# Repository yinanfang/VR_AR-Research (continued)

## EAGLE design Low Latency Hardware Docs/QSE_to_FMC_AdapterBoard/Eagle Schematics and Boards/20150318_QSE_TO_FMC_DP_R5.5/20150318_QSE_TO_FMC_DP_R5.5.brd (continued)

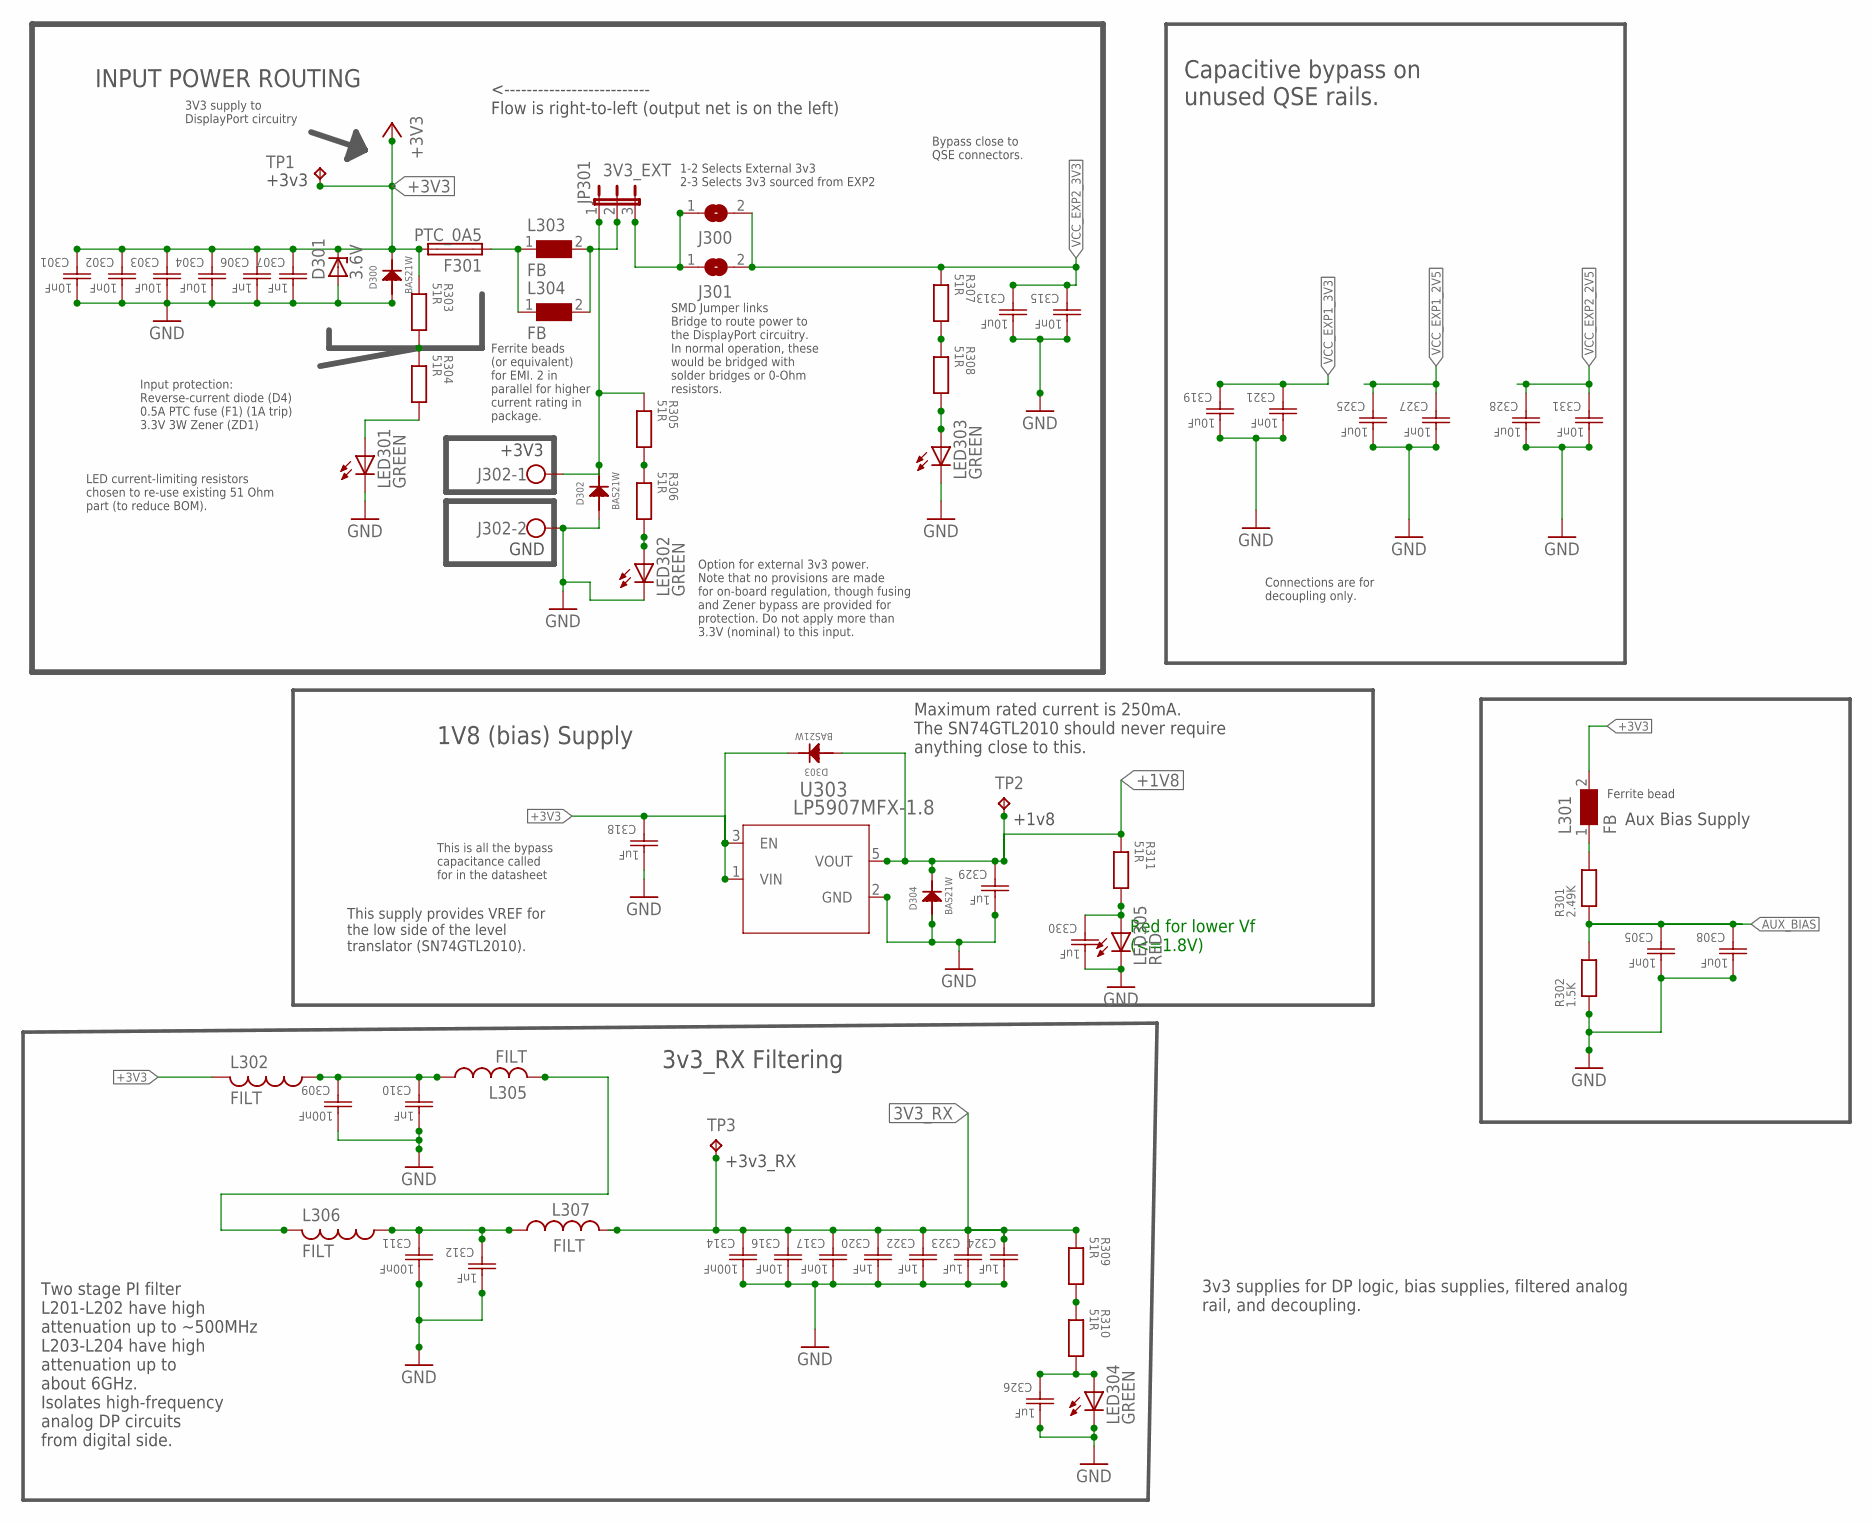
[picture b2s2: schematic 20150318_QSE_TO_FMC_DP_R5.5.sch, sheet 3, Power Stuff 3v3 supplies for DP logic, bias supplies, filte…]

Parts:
C301, C302: 10nF; CAPC1005X60N
C303, C304, C308, C313, C319, C325, C328: 10uF; CAPC1608X85N
C305, C316, C317: 10nF; CAPC1005X60N; PART# GRM1885C1H103JA01
C306, C307, C310, C312, C320, C322: 1nF; CAPC1005X60N; PART# GRM1885C1E102JA01
C309, C311, C314: 100nF; CAPC1005X60N; PART# GRM188B31H104MA92
C315, C321, C327, C331: 10nF; CAPC1608X85N
C318, C329: 1uF; CAPC1005X60N
C323, C324, C326, C330: 1uF; CAPC1005X60N; PART# GRM188B31A225KE33
D300, D302, D303, D304: BAS21W; SOT65P210X100-3N
D301: 3.6V; SMB; PART# 1SMB5914BT3G
F301: PTC_0A5; SMD-0805
J300, J301: SJW
J302: W237-102
JP301: 3V3_EXT; JP2
L301: FB; 0402
L302, L305: FILT; R0603; PART# BLM18HE152SN1
L303, L304: FB; 0805
L306, L307: FILT; R0603; PART# BLM18HE601SN1
LED301, LED302, LED303, LED304: GREEN; CHIP-LED0805; PART# LG R971-KN-1; DIGIKEY_SKU 475-1410-1-ND
LED305: RED; SML0603; PART# 5975112407F; DIGIKEY_SKU 350-2436-6-ND
R301: 2.49K; RESC1005X40N
R302: 1.5K; RESC1005X40N
R303, R304, R305, R306, R307, R308, R309, R310, R311: 51R; RESC1005X40N
TP1: +3v3; TP10R
TP2: +1v8; TP10R
TP3: +3v3_RX; TP10R
U303: LP5907MFX-1.8; DBV5

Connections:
1V8_LED: C330.2 (1), LED305.A, R311.1
3V3_EXP_JP: D302.3 (C), J302.1, JP301.1, R305.2
3V3_INT_JP: J300.1, J301.1, JP301.3
3V3_INT_LED: LED303.A, R308.1
3V3_IN_FILTER_TO_FUSE: F301.1, L303.1, L304.1
3V3_RX: C314.2 (1), C316.2 (1), C317.2 (1), C320.2 (1), C322.2 (1), C323.2 (1), C324.2 (1), L307.2, R309.2, TP3.TP; also elsewhere on the board
3V3_RX_FILT_S0: C309.2 (1), C310.2 (1), L302.1, L305.1
3V3_RX_FILT_S1: L305.2, L306.2
3V3_RX_FILT_S2: C311.2 (1), C312.2 (1), L306.1, L307.1
3V3_RX_LED: C326.2 (1), LED304.A, R310.1
3V3_TO_AUX_BIAS_POST_FILTER: L301.1, R301.1
+1V8: C329.2 (1), D303.1 (A), D304.3 (C), R311.2, TP2.TP, U303.5 (VOUT); also elsewhere on the board
+3V3: C301.2 (1), C302.2 (1), C303.2 (1), C304.2 (1), C306.2 (1), C307.2 (1), C318.2 (1), D300.3 (C), D301.C, D303.3 (C), F301.2, L301.2, L302.2, R303.2, TP1.TP, U303.1 (VIN), U303.3 (EN); also elsewhere on the board
AUX_BIAS: C305.2 (1), C308.2 (1), R301.2, R302.1; also elsewhere on the board
EXT_3V3_LED: LED302.A, R306.1
GND: C301.1 (2), C302.1 (2), C303.1 (2), C304.1 (2), C305.1 (2), C306.1 (2), C307.1 (2), C308.1 (2), C309.1 (2), C310.1 (2), C311.1 (2), C312.1 (2), C313.1 (2), C314.1 (2), C315.1 (2), C316.1 (2), C317.1 (2), C318.1 (2), C319.1 (2), C320.1 (2), C321.1 (2), C322.1 (2), C323.1 (2), C324.1 (2), C325.1 (2), C326.1 (2), C327.1 (2), C328.1 (2), C329.1 (2), C330.1 (2), C331.1 (2), D300.1 (A), D301.A, D302.1 (A), D304.1 (A), J302.2, LED301.C, LED302.C, LED303.C, LED304.C, LED305.C, R302.2, U303.2 (GND); also elsewhere on the board
MAIN_POWER_LED: LED301.A, R304.1
R303_R304: R303.1, R304.2
R306_R305: R305.1, R306.2
R308_R307: R307.1, R308.2
R309_R310: R309.1, R310.2
SELECTED_3V3: JP301.2, L303.2, L304.2
VCC_EXP1_2V5: C325.2 (1), C327.2 (1); also elsewhere on the board
VCC_EXP1_3V3: C319.2 (1), C321.2 (1); also elsewhere on the board
VCC_EXP2_2V5: C328.2 (1), C331.2 (1); also elsewhere on the board
VCC_EXP2_3V3: C313.2 (1), C315.2 (1), J300.2, J301.2, R307.2; also elsewhere on the board

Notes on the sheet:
This supply provides VREF for the low side of the level translator (SN74GTL2010).
Aux Bias Supply
1-2 Selects External 3v3 2-3 Selects 3v3 sourced from EXP2
INPUT POWER ROUTING
SMD Jumper links Bridge to route power to the DisplayPort circuitry. In normal operation, these would be bridged with solder bridges or 0-Ohm resistors.
+3V3
GND
Option for external 3v3 power. Note that no provisions are made for on-board regulation, though fusing and Zener bypass are provided for protection. Do not apply more than 3.3V (nominal) to this input.
Input protection: Reverse-current diode (D4) 0.5A PTC fuse (F1) (1A trip) 3.3V 3W Zener (ZD1)
3V3 supply to DisplayPort circuitry
Bypass close to QSE connectors.
Two stage PI filter L201-L202 have high attenuation up to ~500MHz L203-L204 have high attenuation up to about 6GHz. Isolates high-frequency analog DP circuits from digital side.
Maximum rated current is 250mA. The SN74GTL2010 should never require anything close to this.
This is all the bypass capacitance called for in the datasheet
3v3_RX Filtering
1V8 (bias) Supply
Red for lower Vf (<=1.8V)
Connections are for decoupling only.
Ferrite beads (or equivalent) for EMI. 2 in parallel for higher current rating in package.
LED current-limiting resistors chosen to re-use existing 51 Ohm part (to reduce BOM).
<-------------------------- Flow is right-to-left (output net is on the left)
Ferrite bead
Capacitive bypass on unused QSE rails.
3v3 supplies for DP logic, bias supplies, filtered analog rail, and decoupling.

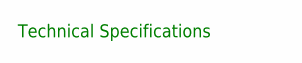
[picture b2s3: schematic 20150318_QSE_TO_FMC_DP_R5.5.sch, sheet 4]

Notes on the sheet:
Technical Specifications

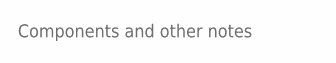
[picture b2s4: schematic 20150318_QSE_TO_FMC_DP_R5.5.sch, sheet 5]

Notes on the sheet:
Components and other notes

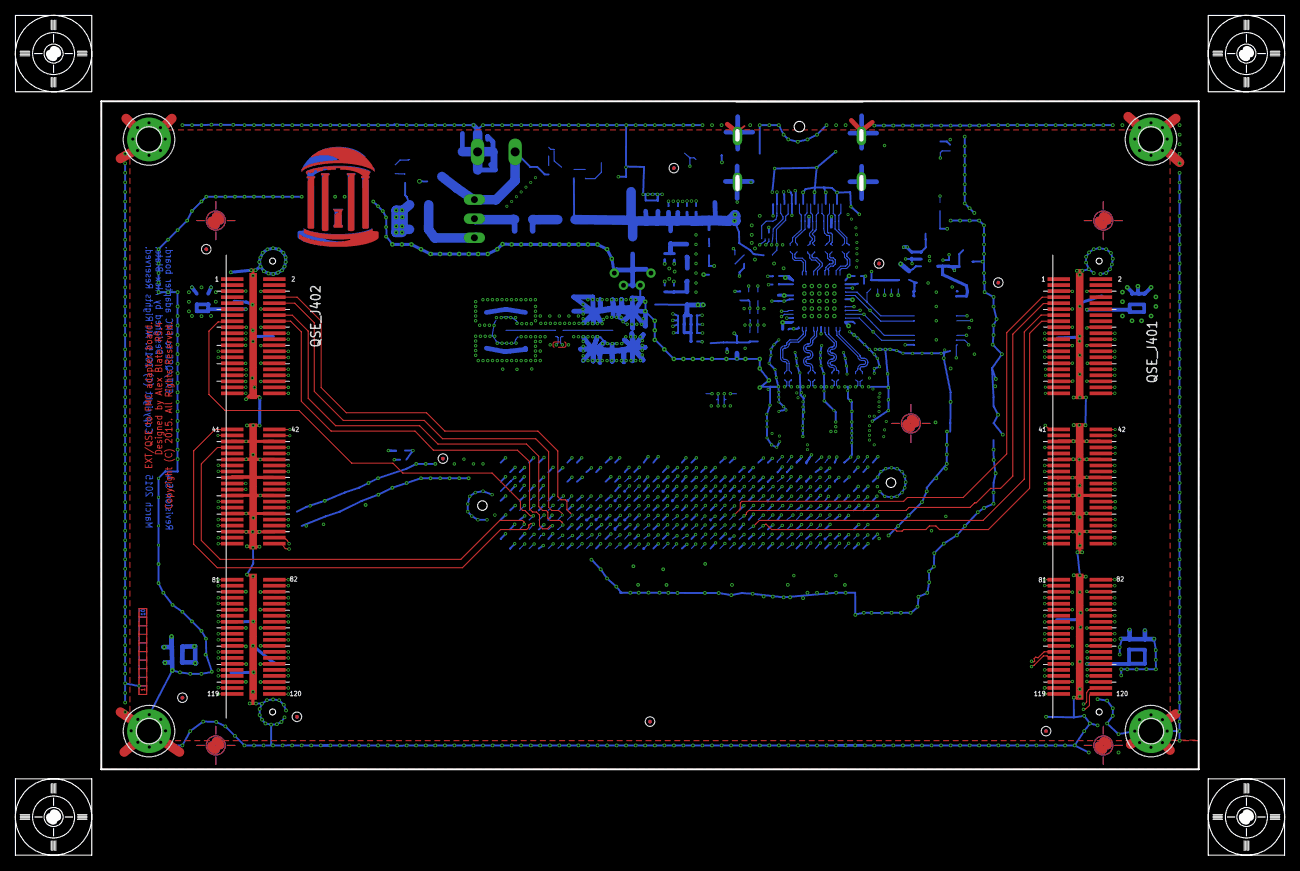
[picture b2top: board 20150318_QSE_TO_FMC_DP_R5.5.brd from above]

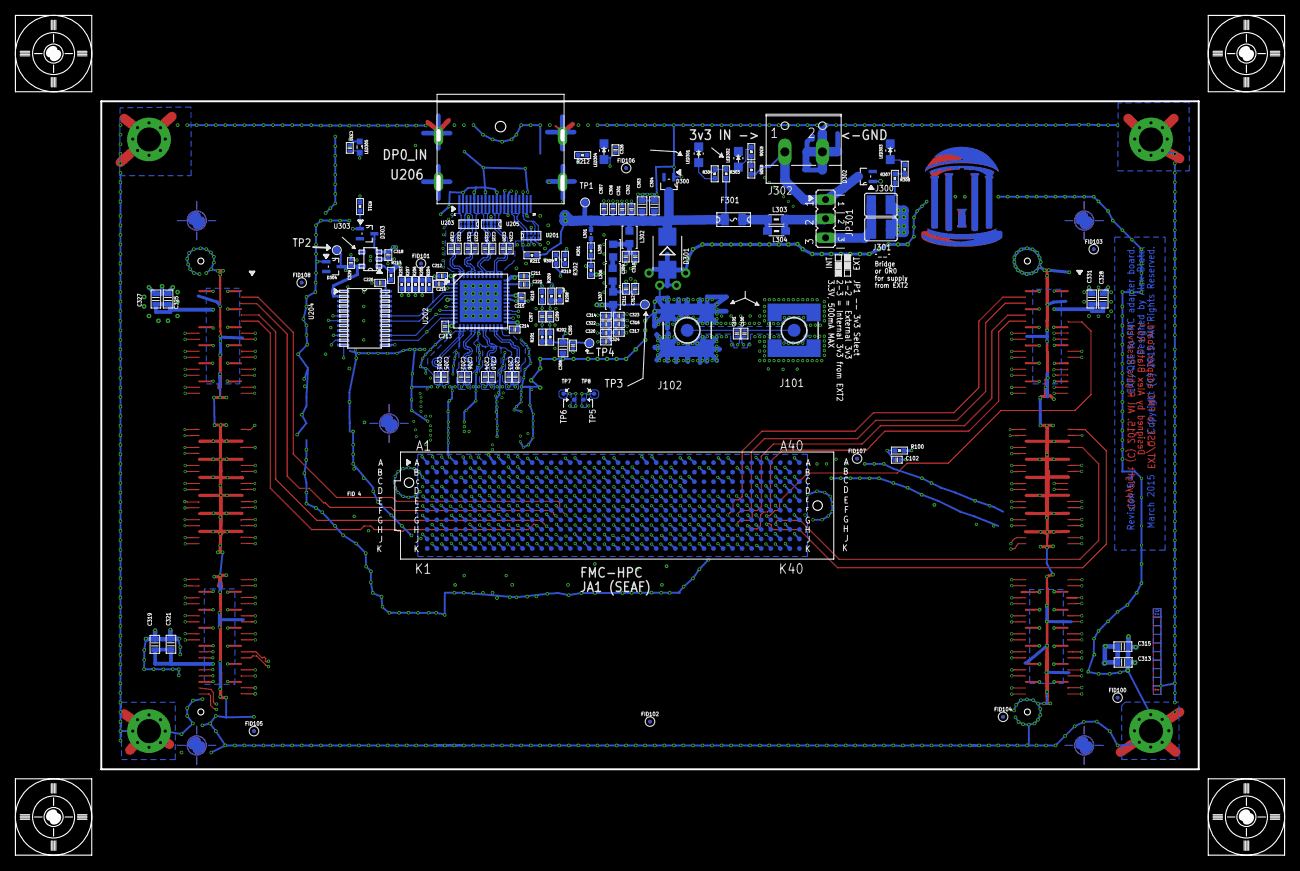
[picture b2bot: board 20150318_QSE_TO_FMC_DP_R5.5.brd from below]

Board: 10 copper layers, 146.1 x 88.9 mm, 149 parts (125 on the bottom side), 236 nets.

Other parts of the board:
FID100, FID101, FID102, FID103, FID104, FID105, FID106, FID107, FID108: FIDUTIAL
J100_FMC:FMC1: >NAME; SEAF-40-10
QSE_J401: EXP1; QSE-060-01
QSE_J402: EXP2; QSE-060-01
U$2, U$3, U$4, U$5, U$6: PASS-ROUND
U$8, U$9, U$10, U$11: ALIGNMENT

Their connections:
DP0_AUX_RX_DIFF_N: J100_FMC:FMC1.H11; also elsewhere on the board
DP0_AUX_RX_DIFF_P: J100_FMC:FMC1.H10; also elsewhere on the board
DP0_CAD: J100_FMC:FMC1.C19; also elsewhere on the board
DP0_HPD: J100_FMC:FMC1.C18; also elsewhere on the board
DP0_LANE0_N: J100_FMC:FMC1.A11; also elsewhere on the board
DP0_LANE0_P: J100_FMC:FMC1.A10; also elsewhere on the board
DP0_LANE1_N: J100_FMC:FMC1.A7; also elsewhere on the board
DP0_LANE1_P: J100_FMC:FMC1.A6; also elsewhere on the board
DP0_LANE2_N: J100_FMC:FMC1.C7; also elsewhere on the board
DP0_LANE2_P: J100_FMC:FMC1.C6; also elsewhere on the board
DP0_LANE3_N: J100_FMC:FMC1.A3; also elsewhere on the board
DP0_LANE3_P: J100_FMC:FMC1.A2; also elsewhere on the board
DP0_RX_ENA: J100_FMC:FMC1.G36; also elsewhere on the board
DP0_RX_SENSE_N: J100_FMC:FMC1.G10; also elsewhere on the board
DP0_RX_SENSE_P: J100_FMC:FMC1.G9; also elsewhere on the board
DP0_SCL_CTL: J100_FMC:FMC1.H31; also elsewhere on the board
DP0_SDA_CTL: J100_FMC:FMC1.H25; also elsewhere on the board
EXP1_DIFF_CLK_IN_CLK2_N: J100_FMC:FMC1.K5, QSE_J401.44
EXP1_DIFF_CLK_IN_CLK2_P: J100_FMC:FMC1.K4, QSE_J401.42
EXP1_DIFF_CLK_OUT_CLK3_N: J100_FMC:FMC1.J3, QSE_J401.74
EXP1_DIFF_CLK_OUT_CLK3_P: J100_FMC:FMC1.J2, QSE_J401.72
EXP2_DIFF_CLK_IN_N: J100_FMC:FMC1.D21, QSE_J402.44
EXP2_DIFF_CLK_IN_P: J100_FMC:FMC1.D20, QSE_J402.42
EXP2_SE_CLK_IN: J100_FMC:FMC1.C22, QSE_J402.43
FMC_3PV3_TERM: J100_FMC:FMC1.C39, J100_FMC:FMC1.D36, J100_FMC:FMC1.D38, J100_FMC:FMC1.D40; also elsewhere on the board
GBCTCLK1_M2C_N: J100_FMC:FMC1.B21; also elsewhere on the board
GBCTCLK1_M2C_P: J100_FMC:FMC1.B20; also elsewhere on the board
GND: J100_FMC:FMC1.A1, J100_FMC:FMC1.A4, J100_FMC:FMC1.A5, J100_FMC:FMC1.A8, J100_FMC:FMC1.A9, J100_FMC:FMC1.A12, J100_FMC:FMC1.A13, J100_FMC:FMC1.A16, J100_FMC:FMC1.A17, J100_FMC:FMC1.A20, J100_FMC:FMC1.A21, J100_FMC:FMC1.A24, J100_FMC:FMC1.A25, J100_FMC:FMC1.A28, J100_FMC:FMC1.A29, J100_FMC:FMC1.A32, J100_FMC:FMC1.A33, J100_FMC:FMC1.A36, J100_FMC:FMC1.A37, J100_FMC:FMC1.A40, J100_FMC:FMC1.B2, J100_FMC:FMC1.B3, J100_FMC:FMC1.B6, J100_FMC:FMC1.B7, J100_FMC:FMC1.B10, J100_FMC:FMC1.B11, J100_FMC:FMC1.B14, J100_FMC:FMC1.B15, J100_FMC:FMC1.B18, J100_FMC:FMC1.B19, J100_FMC:FMC1.B22, J100_FMC:FMC1.B23, J100_FMC:FMC1.B26, J100_FMC:FMC1.B27, J100_FMC:FMC1.B30, J100_FMC:FMC1.B31, J100_FMC:FMC1.B34, J100_FMC:FMC1.B35, J100_FMC:FMC1.B38, J100_FMC:FMC1.B39, J100_FMC:FMC1.C1, J100_FMC:FMC1.C4, J100_FMC:FMC1.C5, J100_FMC:FMC1.C8, J100_FMC:FMC1.C9, J100_FMC:FMC1.C12, J100_FMC:FMC1.C13, J100_FMC:FMC1.C16, J100_FMC:FMC1.C17, J100_FMC:FMC1.C20, J100_FMC:FMC1.C21, J100_FMC:FMC1.C23, J100_FMC:FMC1.C24, J100_FMC:FMC1.C25, J100_FMC:FMC1.C28, J100_FMC:FMC1.C29, J100_FMC:FMC1.C32, J100_FMC:FMC1.C33, J100_FMC:FMC1.C36, J100_FMC:FMC1.C38, J100_FMC:FMC1.C40, J100_FMC:FMC1.D2, J100_FMC:FMC1.D3, J100_FMC:FMC1.D6, J100_FMC:FMC1.D7, J100_FMC:FMC1.D10, J100_FMC:FMC1.D13, J100_FMC:FMC1.D16, J100_FMC:FMC1.D19, J100_FMC:FMC1.D22, J100_FMC:FMC1.D25, J100_FMC:FMC1.D28, J100_FMC:FMC1.D37, J100_FMC:FMC1.D39, J100_FMC:FMC1.E1, J100_FMC:FMC1.E4, J100_FMC:FMC1.E5, J100_FMC:FMC1.E8, J100_FMC:FMC1.E11, J100_FMC:FMC1.E14, J100_FMC:FMC1.E17, J100_FMC:FMC1.E20, J100_FMC:FMC1.E23, J100_FMC:FMC1.E26, J100_FMC:FMC1.E29, J100_FMC:FMC1.E32, J100_FMC:FMC1.E35, J100_FMC:FMC1.E38, J100_FMC:FMC1.E40, J100_FMC:FMC1.F2, J100_FMC:FMC1.F3, J100_FMC:FMC1.F6, J100_FMC:FMC1.F9, J100_FMC:FMC1.F12, J100_FMC:FMC1.F15, J100_FMC:FMC1.F18, J100_FMC:FMC1.F21, J100_FMC:FMC1.F24, J100_FMC:FMC1.F27, J100_FMC:FMC1.F30, J100_FMC:FMC1.F33, J100_FMC:FMC1.F36, J100_FMC:FMC1.F39, J100_FMC:FMC1.G1, J100_FMC:FMC1.G4, J100_FMC:FMC1.G5, J100_FMC:FMC1.G8, J100_FMC:FMC1.G11, J100_FMC:FMC1.G14, J100_FMC:FMC1.G17, J100_FMC:FMC1.G20, J100_FMC:FMC1.G23, J100_FMC:FMC1.G26, J100_FMC:FMC1.G29, J100_FMC:FMC1.G32, J100_FMC:FMC1.G35, J100_FMC:FMC1.G38, J100_FMC:FMC1.G40, J100_FMC:FMC1.H3, J100_FMC:FMC1.H6, J100_FMC:FMC1.H9, J100_FMC:FMC1.H12, J100_FMC:FMC1.H15, J100_FMC:FMC1.H18, J100_FMC:FMC1.H21, J100_FMC:FMC1.H24, J100_FMC:FMC1.H26, J100_FMC:FMC1.H27, J100_FMC:FMC1.H30, J100_FMC:FMC1.H32, J100_FMC:FMC1.H33, J100_FMC:FMC1.H36, J100_FMC:FMC1.H39, J100_FMC:FMC1.J1, J100_FMC:FMC1.J4, J100_FMC:FMC1.J5, J100_FMC:FMC1.J8, J100_FMC:FMC1.J11, J100_FMC:FMC1.J14, J100_FMC:FMC1.J17, J100_FMC:FMC1.J20, J100_FMC:FMC1.J23, J100_FMC:FMC1.J26, J100_FMC:FMC1.J29, J100_FMC:FMC1.J32, J100_FMC:FMC1.J35, J100_FMC:FMC1.J38, J100_FMC:FMC1.J40, J100_FMC:FMC1.K2, J100_FMC:FMC1.K3, J100_FMC:FMC1.K6, J100_FMC:FMC1.K9, J100_FMC:FMC1.K12, J100_FMC:FMC1.K15, J100_FMC:FMC1.K18, J100_FMC:FMC1.K21, J100_FMC:FMC1.K24, J100_FMC:FMC1.K27, J100_FMC:FMC1.K30, J100_FMC:FMC1.K33, J100_FMC:FMC1.K36, J100_FMC:FMC1.K39, QSE_J401.45, QSE_J401.46, QSE_J401.51, QSE_J401.52, QSE_J401.57, QSE_J401.58, QSE_J401.63, QSE_J401.64, QSE_J401.69, QSE_J401.70, QSE_J401.75, QSE_J401.76, QSE_J401.GND1, QSE_J401.GND2, QSE_J401.GND3, QSE_J401.GND4, QSE_J401.GND5, QSE_J401.GND6, QSE_J401.GND7, QSE_J401.GND8, QSE_J401.GND9, QSE_J401.GND10, QSE_J401.GND11, QSE_J401.GND12, QSE_J402.45, QSE_J402.46, QSE_J402.51, QSE_J402.52, QSE_J402.57, QSE_J402.58, QSE_J402.63, QSE_J402.64, QSE_J402.69, QSE_J402.70, QSE_J402.75, QSE_J402.76, QSE_J402.GND1, QSE_J402.GND2, QSE_J402.GND3, QSE_J402.GND4, QSE_J402.GND5, QSE_J402.GND6, QSE_J402.GND7, QSE_J402.GND8, QSE_J402.GND9, QSE_J402.GND10, QSE_J402.GND11, QSE_J402.GND12; also elsewhere on the board
GPIO_0: J100_FMC:FMC1.H37, QSE_J402.41
GPIO_1: J100_FMC:FMC1.H38, QSE_J402.47
GPIO_2: J100_FMC:FMC1.H34, QSE_J402.14
GPIO_3: J100_FMC:FMC1.H35, QSE_J402.16
GPIO_4: J100_FMC:FMC1.G34, QSE_J402.10
GPIO_5: J100_FMC:FMC1.G33, QSE_J402.8
GPIO_6: J100_FMC:FMC1.H14, QSE_J401.13
GPIO_7: J100_FMC:FMC1.H13, QSE_J401.15
GPIO_8: J100_FMC:FMC1.G16, QSE_J401.7
GPIO_9: J100_FMC:FMC1.G15, QSE_J401.9
GPIO_10: J100_FMC:FMC1.G37, QSE_J402.15
HDP0_N: J100_FMC:FMC1.F5, QSE_J401.33
HDP0_P: J100_FMC:FMC1.F4, QSE_J401.31
HDP1_N: J100_FMC:FMC1.E3, QSE_J401.39
HDP1_P: J100_FMC:FMC1.E2, QSE_J401.37
HDP2_N: J100_FMC:FMC1.K8, QSE_J401.55
HDP2_P: J100_FMC:FMC1.K7, QSE_J401.53
HDP3_N: J100_FMC:FMC1.J7, QSE_J401.56
HDP3_P: J100_FMC:FMC1.J6, QSE_J401.54
HDP4_N: J100_FMC:FMC1.F8, QSE_J401.67
HDP4_P: J100_FMC:FMC1.F7, QSE_J401.65
HDP5_N: J100_FMC:FMC1.E7, QSE_J401.62
HDP5_P: J100_FMC:FMC1.E6, QSE_J401.60
HDP6_N: J100_FMC:FMC1.K11, QSE_J401.73
HDP6_P: J100_FMC:FMC1.K10, QSE_J401.71
HDP7_N: J100_FMC:FMC1.J10, QSE_J401.68
HDP7_P: J100_FMC:FMC1.J9, QSE_J401.66
HDP8_N: J100_FMC:FMC1.F11, QSE_J401.79
HDP8_P: J100_FMC:FMC1.F10, QSE_J401.77
HDP9_N: J100_FMC:FMC1.E10, QSE_J401.80
HDP9_P: J100_FMC:FMC1.E9, QSE_J401.78
HDP10_N: J100_FMC:FMC1.K14, QSE_J401.83
HDP10_P: J100_FMC:FMC1.K13, QSE_J401.81
HDP11_N: J100_FMC:FMC1.J13, QSE_J401.84
HDP11_P: J100_FMC:FMC1.J12, QSE_J401.82
HDP12_N: J100_FMC:FMC1.F14, QSE_J401.89
HDP12_P: J100_FMC:FMC1.F13, QSE_J401.87
HDP13_N: J100_FMC:FMC1.E13, QSE_J401.90
HDP13_P: J100_FMC:FMC1.E12, QSE_J401.88
HDP14_N: J100_FMC:FMC1.J16, QSE_J401.95
HDP14_P: J100_FMC:FMC1.J15, QSE_J401.93
HDP15_N: J100_FMC:FMC1.F17, QSE_J401.96
HDP15_P: J100_FMC:FMC1.F16, QSE_J401.94
HDP16_N: J100_FMC:FMC1.E16, QSE_J401.101
HDP16_P: J100_FMC:FMC1.E15, QSE_J401.99
HDP17_N: J100_FMC:FMC1.K17, QSE_J401.102
HDP17_P: J100_FMC:FMC1.K16, QSE_J401.100
HDP18_N: J100_FMC:FMC1.J19, QSE_J401.107
HDP18_P: J100_FMC:FMC1.J18, QSE_J401.105
HDP19_N: J100_FMC:FMC1.F20, QSE_J401.108
HDP19_P: J100_FMC:FMC1.F19, QSE_J401.106
HDP20_N: J100_FMC:FMC1.E19, QSE_J401.113
HDP20_P: J100_FMC:FMC1.E18, QSE_J401.111
HDP21_N: J100_FMC:FMC1.K20, QSE_J401.114
HDP21_P: J100_FMC:FMC1.K19, QSE_J401.112
HDP22_N: J100_FMC:FMC1.J22, QSE_J401.119
HDP22_P: J100_FMC:FMC1.J21, QSE_J401.117
HDP23_N: J100_FMC:FMC1.K23, QSE_J401.120
HDP23_P: J100_FMC:FMC1.K22, QSE_J401.118
HDQ0_N: J100_FMC:FMC1.K26, QSE_J402.120
HDQ0_P: J100_FMC:FMC1.K25, QSE_J402.118
HDQ1_N: J100_FMC:FMC1.J25, QSE_J402.119
HDQ1_P: J100_FMC:FMC1.J24, QSE_J402.117
HDQ2_N: J100_FMC:FMC1.F23, QSE_J402.114
HDQ2_P: J100_FMC:FMC1.F22, QSE_J402.112
HDQ3_N: J100_FMC:FMC1.E22, QSE_J402.113
HDQ3_P: J100_FMC:FMC1.E21, QSE_J402.111
HDQ4_N: J100_FMC:FMC1.F26, QSE_J402.108
HDQ4_P: J100_FMC:FMC1.F25, QSE_J402.106
HDQ5_N: J100_FMC:FMC1.E25, QSE_J402.107
HDQ5_P: J100_FMC:FMC1.E24, QSE_J402.105
HDQ6_N: J100_FMC:FMC1.K29, QSE_J402.102
HDQ6_P: J100_FMC:FMC1.K28, QSE_J402.100
HDQ7_N: J100_FMC:FMC1.J28, QSE_J402.101
HDQ7_P: J100_FMC:FMC1.J27, QSE_J402.99
HDQ8_N: J100_FMC:FMC1.F29, QSE_J402.96
HDQ8_P: J100_FMC:FMC1.F28, QSE_J402.94
HDQ9_N: J100_FMC:FMC1.E28, QSE_J402.95
HDQ9_P: J100_FMC:FMC1.E27, QSE_J402.93
HDQ10_N: J100_FMC:FMC1.K32, QSE_J402.90
HDQ10_P: J100_FMC:FMC1.K31, QSE_J402.88
HDQ11_N: J100_FMC:FMC1.J31, QSE_J402.89
HDQ11_P: J100_FMC:FMC1.J30, QSE_J402.87
HDQ12_N: J100_FMC:FMC1.F32, QSE_J402.84
HDQ12_P: J100_FMC:FMC1.F31, QSE_J402.82
HDQ13_N: J100_FMC:FMC1.E31, QSE_J402.83
HDQ13_P: J100_FMC:FMC1.E30, QSE_J402.81
HDQ14_N: J100_FMC:FMC1.K35, QSE_J402.80
HDQ14_P: J100_FMC:FMC1.K34, QSE_J402.78
HDQ15_N: J100_FMC:FMC1.J34, QSE_J402.79
HDQ15_P: J100_FMC:FMC1.J33, QSE_J402.77
HDQ16_N: J100_FMC:FMC1.F35, QSE_J402.68
HDQ16_P: J100_FMC:FMC1.F34, QSE_J402.66
HDQ17_N: J100_FMC:FMC1.K38, QSE_J402.73
HDQ17_P: J100_FMC:FMC1.K37, QSE_J402.71
HDQ18_N: J100_FMC:FMC1.J37, QSE_J402.62
HDQ18_P: J100_FMC:FMC1.J36, QSE_J402.60
HDQ19_N: J100_FMC:FMC1.E34, QSE_J402.67
HDQ19_P: J100_FMC:FMC1.E33, QSE_J402.65
HDQ20_N: J100_FMC:FMC1.F38, QSE_J402.56
HDQ20_P: J100_FMC:FMC1.F37, QSE_J402.54
HDQ21_N: J100_FMC:FMC1.E37, QSE_J402.55
HDQ21_P: J100_FMC:FMC1.E36, QSE_J402.53
LA00_N: J100_FMC:FMC1.G7, QSE_J401.61
LA00_P: J100_FMC:FMC1.G6, QSE_J401.59
LA01_N: J100_FMC:FMC1.D9, QSE_J401.50
LA01_P: J100_FMC:FMC1.D8, QSE_J401.48
LA02_N: J100_FMC:FMC1.H8, QSE_J402.74
LA02_P: J100_FMC:FMC1.H7, QSE_J402.72
LA05_N: J100_FMC:FMC1.D12, QSE_J401.34
LA05_P: J100_FMC:FMC1.D11, QSE_J401.32
LA06_N: J100_FMC:FMC1.C11, QSE_J401.40
LA06_P: J100_FMC:FMC1.C10, QSE_J401.38
LA08_N: J100_FMC:FMC1.G13, QSE_J401.28
LA08_P: J100_FMC:FMC1.G12, QSE_J401.26
LA09_N: J100_FMC:FMC1.D15, QSE_J401.22
LA09_P: J100_FMC:FMC1.D14, QSE_J401.20
LA10_N: J100_FMC:FMC1.C15, QSE_J401.27
LA10_P: J100_FMC:FMC1.C14, QSE_J401.25
LA13_N: J100_FMC:FMC1.D18, QSE_J401.21
LA13_P: J100_FMC:FMC1.D17, QSE_J401.19
LA16_N: J100_FMC:FMC1.G19, QSE_J402.50
LA16_P: J100_FMC:FMC1.G18, QSE_J402.48
LA19_N: J100_FMC:FMC1.H23, QSE_J402.39
LA19_P: J100_FMC:FMC1.H22, QSE_J402.37
LA20_N: J100_FMC:FMC1.G22, QSE_J402.22
LA20_P: J100_FMC:FMC1.G21, QSE_J402.20
LA22_N: J100_FMC:FMC1.G25, QSE_J402.28
LA22_P: J100_FMC:FMC1.G24, QSE_J402.26
LA23_N: J100_FMC:FMC1.D24, QSE_J402.21
LA23_P: J100_FMC:FMC1.D23, QSE_J402.19
LA24_N: J100_FMC:FMC1.H29, QSE_J402.61
LA24_P: J100_FMC:FMC1.H28, QSE_J402.59
LA25_N: J100_FMC:FMC1.G28, QSE_J402.27
LA25_P: J100_FMC:FMC1.G27, QSE_J402.25
LA26_N: J100_FMC:FMC1.D27, QSE_J402.34
LA26_P: J100_FMC:FMC1.D26, QSE_J402.32
LA27_N: J100_FMC:FMC1.C27, QSE_J402.33
LA27_P: J100_FMC:FMC1.C26, QSE_J402.31
LA29_N: J100_FMC:FMC1.G31, QSE_J402.40
LA29_P: J100_FMC:FMC1.G30, QSE_J402.38
LOOP0_N: J100_FMC:FMC1.H17, J100_FMC:FMC1.H20; also elsewhere on the board
LOOP0_P: J100_FMC:FMC1.H16, J100_FMC:FMC1.H19; also elsewhere on the board
PG_M2C: J100_FMC:FMC1.F1, QSE_J401.47
PRSNT_M2C_L: J100_FMC:FMC1.H2, QSE_J401.41
VCC_EXP1_2V5: QSE_J401.5, QSE_J401.6, QSE_J401.11, QSE_J401.12, QSE_J401.17, QSE_J401.18, QSE_J401.23, QSE_J401.24, QSE_J401.29, QSE_J401.30, QSE_J401.35, QSE_J401.36; also elsewhere on the board
VCC_EXP1_3V3: QSE_J401.85, QSE_J401.86, QSE_J401.91, QSE_J401.92, QSE_J401.97, QSE_J401.98, QSE_J401.103, QSE_J401.104, QSE_J401.109, QSE_J401.110, QSE_J401.115, QSE_J401.116; also elsewhere on the board
VCC_EXP2_2V5: QSE_J402.5, QSE_J402.6, QSE_J402.11, QSE_J402.12, QSE_J402.17, QSE_J402.18, QSE_J402.23, QSE_J402.24, QSE_J402.29, QSE_J402.30, QSE_J402.35, QSE_J402.36; also elsewhere on the board
VCC_EXP2_3V3: QSE_J402.85, QSE_J402.86, QSE_J402.91, QSE_J402.92, QSE_J402.97, QSE_J402.98, QSE_J402.103, QSE_J402.104, QSE_J402.109, QSE_J402.110, QSE_J402.115, QSE_J402.116; also elsewhere on the board

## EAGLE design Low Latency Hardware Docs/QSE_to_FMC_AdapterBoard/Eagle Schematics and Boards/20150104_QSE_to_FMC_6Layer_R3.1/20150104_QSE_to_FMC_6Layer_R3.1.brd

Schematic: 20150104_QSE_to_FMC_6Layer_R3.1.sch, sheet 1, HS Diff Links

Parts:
C1, C3, C5, C7, C9, C11: 10u; C0805; MPN C0805C106K9PACTU
C2, C4, C6, C8, C10, C12: 10n; C0805; MPN 0805YA103JAT2A
H1, H2, H3: MOUNT-PAD-ROUND3.2; 3,2-PAD

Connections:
+2V5: C9.1, C10.1, C11.1, C12.1; also elsewhere on the board
+3V3: C1.1, C2.1, C3.1, C4.1, C5.1, C6.1, C7.1, C8.1; also elsewhere on the board
GND: C1.2, C2.2, C3.2, C4.2, C5.2, C6.2, C7.2, C8.2, C9.2, C10.2, C11.2, C12.2, H1.B3,2, H2.B3,2, H3.B3,2; also elsewhere on the board

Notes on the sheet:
Connections between EXT1 and EXT2 QST connectors and FMC connector. Also present are two 100mil headers bringing out the remaining GPIOs from the EXT connectors.
Values are nominal; board sized for 0805 SMD.
3v3 bypass at: EXT1/EXT2 termination, FMC termination, and off-board connection.
2v5 bypass at EXT1/EXT2 termination
Remaining, non-differential IOs on the EXT sockets are brought out to 0.1" pin headers for use as GPIOs. I couldn't find any more useful pins on the FMC that Xilinx typically ties into... and I'm not sure I can get much more on board without adding another layer.
All nets ending in _P or _N are differential pairs; from what I can tell, the H* stuff is meant for higher-speed; the L* stuff can be used differentially or single-ended. I have routed everything differentially, so, for single-ended use, you would tie the _N line to GND.
I managed to balance all of the differential pairs to 3.3" (3300mil) to a tolerance of 25mil so you can run you busses however you need to without the adapter adding time skew. This tolerance is based on the DDR2 spec.
Although they are not specifically rated for differential use, I routed the GPIOs differentially based on the adjacent pinouts on the EXT2 connectors and with ground guards at the 0.1" connectors.
The +3v3 rail is present on both EXT connectors and the FMC connector. I have tied them all together and added bypass capacitance in strategic places.
3.2mm mounting holes, tied to ground plane.

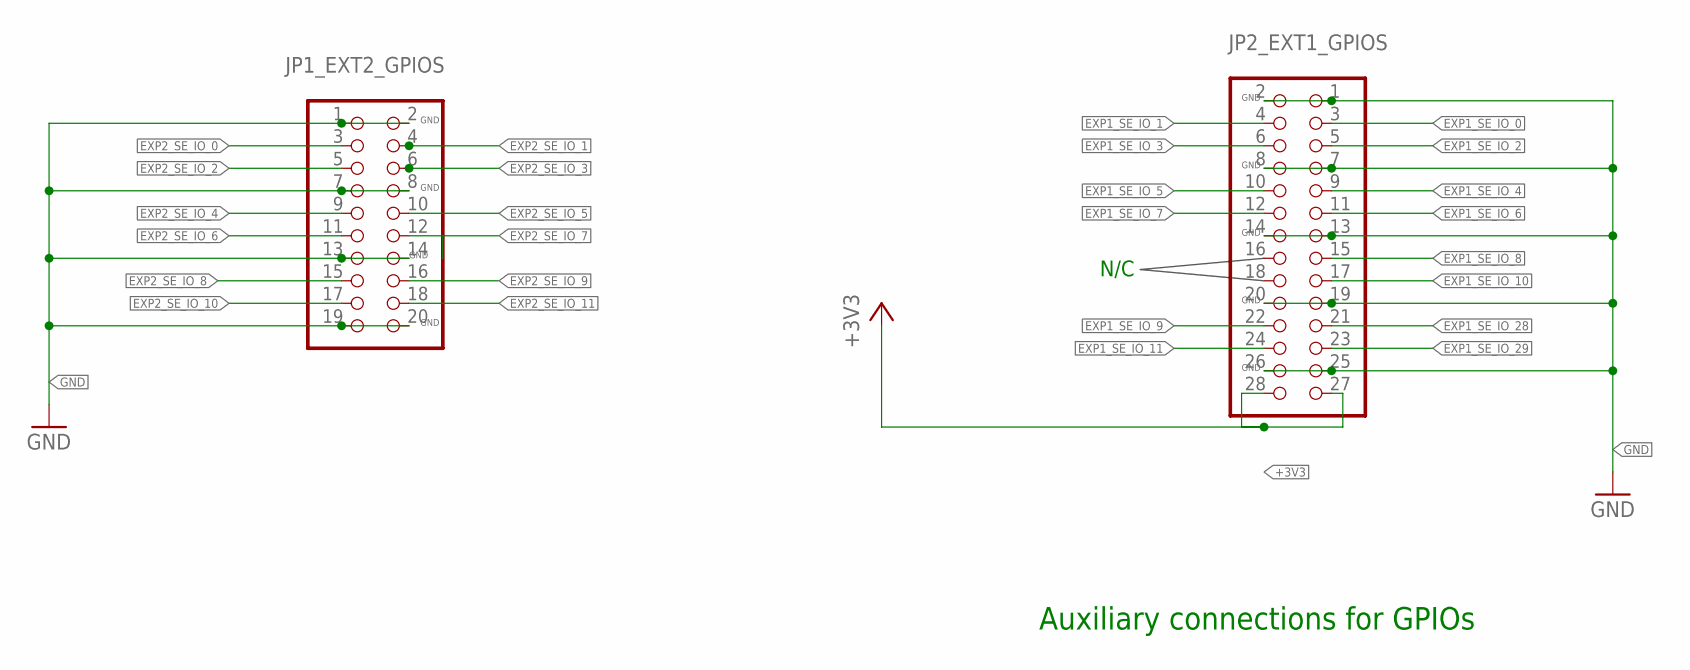
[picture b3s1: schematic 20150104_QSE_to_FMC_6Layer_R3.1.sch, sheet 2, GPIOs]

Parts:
JP1_EXT2_GPIOS: PINHD-2X10; 2X10; MPN 5-146257-5
JP2_EXT1_GPIOS: PINHD-2X14; 2X14; MPN TSW-107-14-S-D

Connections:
+3V3: JP2_EXT1_GPIOS.27, JP2_EXT1_GPIOS.28; also elsewhere on the board
EXP1_SE_IO_0: JP2_EXT1_GPIOS.3; also elsewhere on the board
EXP1_SE_IO_1: JP2_EXT1_GPIOS.4; also elsewhere on the board
EXP1_SE_IO_2: JP2_EXT1_GPIOS.5; also elsewhere on the board
EXP1_SE_IO_3: JP2_EXT1_GPIOS.6; also elsewhere on the board
EXP1_SE_IO_4: JP2_EXT1_GPIOS.9; also elsewhere on the board
EXP1_SE_IO_5: JP2_EXT1_GPIOS.10; also elsewhere on the board
EXP1_SE_IO_6: JP2_EXT1_GPIOS.11; also elsewhere on the board
EXP1_SE_IO_7: JP2_EXT1_GPIOS.12; also elsewhere on the board
EXP1_SE_IO_8: JP2_EXT1_GPIOS.15; also elsewhere on the board
EXP1_SE_IO_9: JP2_EXT1_GPIOS.22; also elsewhere on the board
EXP1_SE_IO_10: JP2_EXT1_GPIOS.17; also elsewhere on the board
EXP1_SE_IO_11: JP2_EXT1_GPIOS.24; also elsewhere on the board
EXP1_SE_IO_28: JP2_EXT1_GPIOS.21; also elsewhere on the board
EXP1_SE_IO_29: JP2_EXT1_GPIOS.23; also elsewhere on the board
EXP2_SE_IO_0: JP1_EXT2_GPIOS.3; also elsewhere on the board
EXP2_SE_IO_1: JP1_EXT2_GPIOS.4; also elsewhere on the board
EXP2_SE_IO_2: JP1_EXT2_GPIOS.5; also elsewhere on the board
EXP2_SE_IO_3: JP1_EXT2_GPIOS.6; also elsewhere on the board
EXP2_SE_IO_4: JP1_EXT2_GPIOS.9; also elsewhere on the board
EXP2_SE_IO_5: JP1_EXT2_GPIOS.10; also elsewhere on the board
EXP2_SE_IO_6: JP1_EXT2_GPIOS.11; also elsewhere on the board
EXP2_SE_IO_7: JP1_EXT2_GPIOS.12; also elsewhere on the board
EXP2_SE_IO_8: JP1_EXT2_GPIOS.15; also elsewhere on the board
EXP2_SE_IO_9: JP1_EXT2_GPIOS.16; also elsewhere on the board
EXP2_SE_IO_10: JP1_EXT2_GPIOS.17; also elsewhere on the board
EXP2_SE_IO_11: JP1_EXT2_GPIOS.18; also elsewhere on the board
GND: JP1_EXT2_GPIOS.1, JP1_EXT2_GPIOS.2, JP1_EXT2_GPIOS.7, JP1_EXT2_GPIOS.8, JP1_EXT2_GPIOS.13, JP1_EXT2_GPIOS.14, JP1_EXT2_GPIOS.19, JP1_EXT2_GPIOS.20, JP2_EXT1_GPIOS.1, JP2_EXT1_GPIOS.2, JP2_EXT1_GPIOS.7, JP2_EXT1_GPIOS.8, JP2_EXT1_GPIOS.13, JP2_EXT1_GPIOS.14, JP2_EXT1_GPIOS.19, JP2_EXT1_GPIOS.20, JP2_EXT1_GPIOS.25, JP2_EXT1_GPIOS.26; also elsewhere on the board

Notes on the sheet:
Auxiliary connections for GPIOs
N/C
